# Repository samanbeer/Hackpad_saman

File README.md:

Thanks [HackClub](https://blueprint.hackclub.com/hackpad)

**Inspiration:**

    Saw a lot of similar MacroPads so i made one myself. Planning to make a better new one after I test this one.

**Challenges**

    The biggest challenge was making the Case for it in Fusion 360, but I am satisfied about the result. Routing the PCB routes was pretty easy after I understood the logic, it was pretty fun.

BOM:

    6x Cherry MX switches
    6x blank DSA keycaps
    1x Seeed XIAO RP2040 (THT)
    1x PCB
    4x M3 x 7mm screws

    Others:
    KMK firmware
    Top and Bottom step file of Case.

Images:

| Case          | Schematic     | PCB  |
| ----------- |:-----------:| --------|
|  | |  |

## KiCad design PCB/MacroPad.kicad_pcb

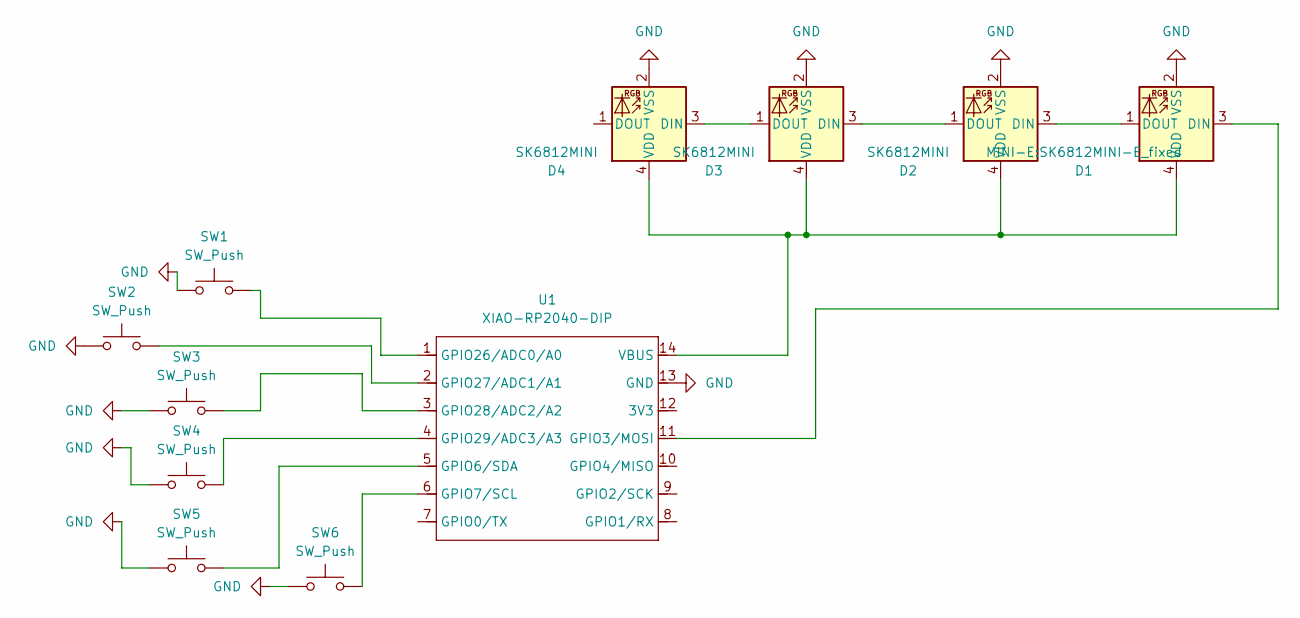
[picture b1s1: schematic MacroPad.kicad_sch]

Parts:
D1: MINI-E:SK6812MINI-E_fixed; SK6812MINI-E_fixed
D2, D3, D4: SK6812MINI; SK6812MINI-E_fixed
SW1, SW2, SW3, SW4, SW5, SW6: SW_Push; SW_Cherry_MX_1.00u_PCB
U1: XIAO-RP2040-DIP

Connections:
GND: D1.2 (VSS), D2.2 (VSS), D3.2 (VSS), D4.2 (VSS), SW1.1, SW2.1, SW3.1, SW4.1, SW5.1, SW6.1, U1.13 (GND)
unnamed: D1.3 (DIN), U1.11 (GPIO3/MOSI)
unnamed: D1.1 (DOUT), D2.3 (DIN)
unnamed: D1.4 (VDD), D2.4 (VDD), D3.4 (VDD), D4.4 (VDD), U1.14 (VBUS)
unnamed: D2.1 (DOUT), D3.3 (DIN)
unnamed: D3.1 (DOUT), D4.3 (DIN)
unnamed: SW5.2, U1.5 (GPIO6/SDA)
unnamed: SW6.2, U1.6 (GPIO7/SCL)
unnamed: SW1.2, U1.1 (GPIO26/ADC0/A0)
unnamed: SW2.2, U1.2 (GPIO27/ADC1/A1)
unnamed: SW3.2, U1.3 (GPIO28/ADC2/A2)
unnamed: SW4.2, U1.4 (GPIO29/ADC3/A3)

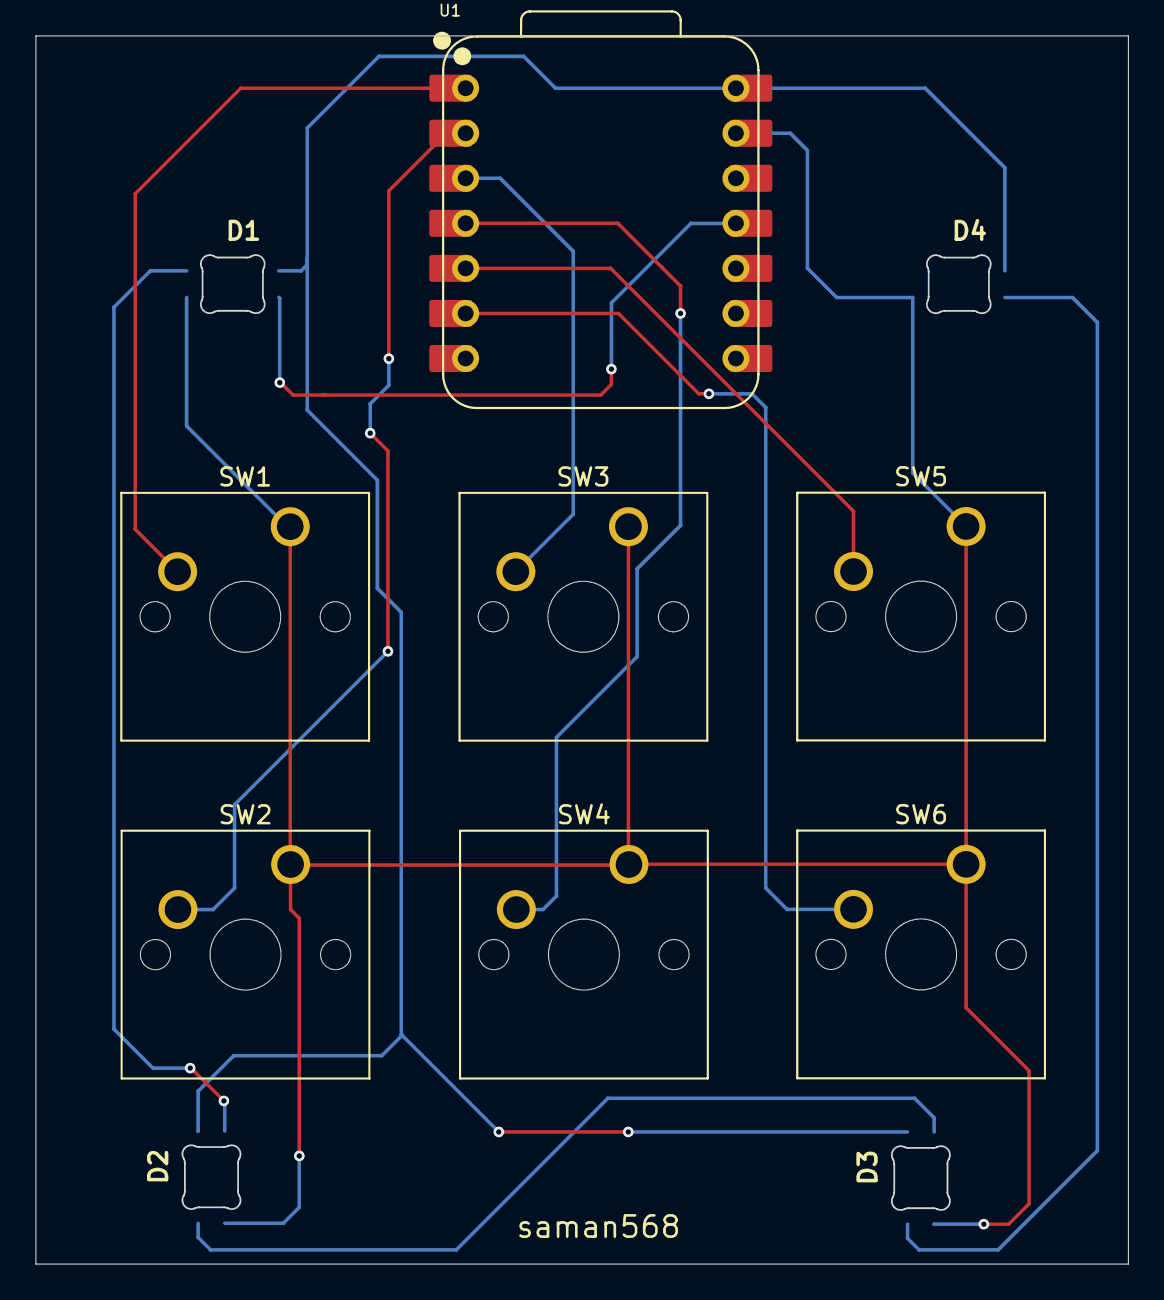
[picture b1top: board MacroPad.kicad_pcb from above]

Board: 2 copper layers, 61.5 x 69.2 mm, 11 parts (0 on the bottom side), 12 nets.

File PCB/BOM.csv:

"Reference","Qty","Value","DNP","Exclude from BOM","Exclude from Board","Footprint","Datasheet"
"D1","1","MINI-E:SK6812MINI-E_fixed","","","","MINI-E:SK6812MINI-E_fixed","https://cdn-shop.adafruit.com/product-files/2686/SK6812MINI_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"
"D2,D3,D4","3","SK6812MINI","","","","MINI-E:SK6812MINI-E_fixed","https://cdn-shop.adafruit.com/product-files/2686/SK6812MINI_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"
"SW1,SW2,SW3,SW4,SW5,SW6","6","SW_Push","","","","Button_Switch_Keyboard:SW_Cherry_MX_1.00u_PCB","~"
"U1","1","XIAO-RP2040-DIP","","","","Seeed Studio XIAO Series Library:XIAO-RP2040-DIP",""

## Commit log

2025-12-21 temp
2025-12-21 Create a
2025-12-23 Document project inspiration and BOM details
    Added project inspiration, challenges faced, and a bill of materials (BOM) for the MacroPad.
2025-12-23 Added images of CAD PCB and SCHEMATICS
2025-12-23 Fix Markdown link formatting in README.md
2025-12-23 added images and repaired not working links
2025-12-24 fixed wrong footprint for SK6812MINI-E
2025-12-24 added BOM.csv
2025-12-25 Added rendered image
2025-12-25 Add rendered image to README
2025-12-25 Correct image links for PCB and CAD in README
    Updated image links for PCB and CAD to use consistent URLs.
2026-02-10 Update journal entry with project note
2026-02-10 final
2026-02-10 Update README with new PCB image and content changes
